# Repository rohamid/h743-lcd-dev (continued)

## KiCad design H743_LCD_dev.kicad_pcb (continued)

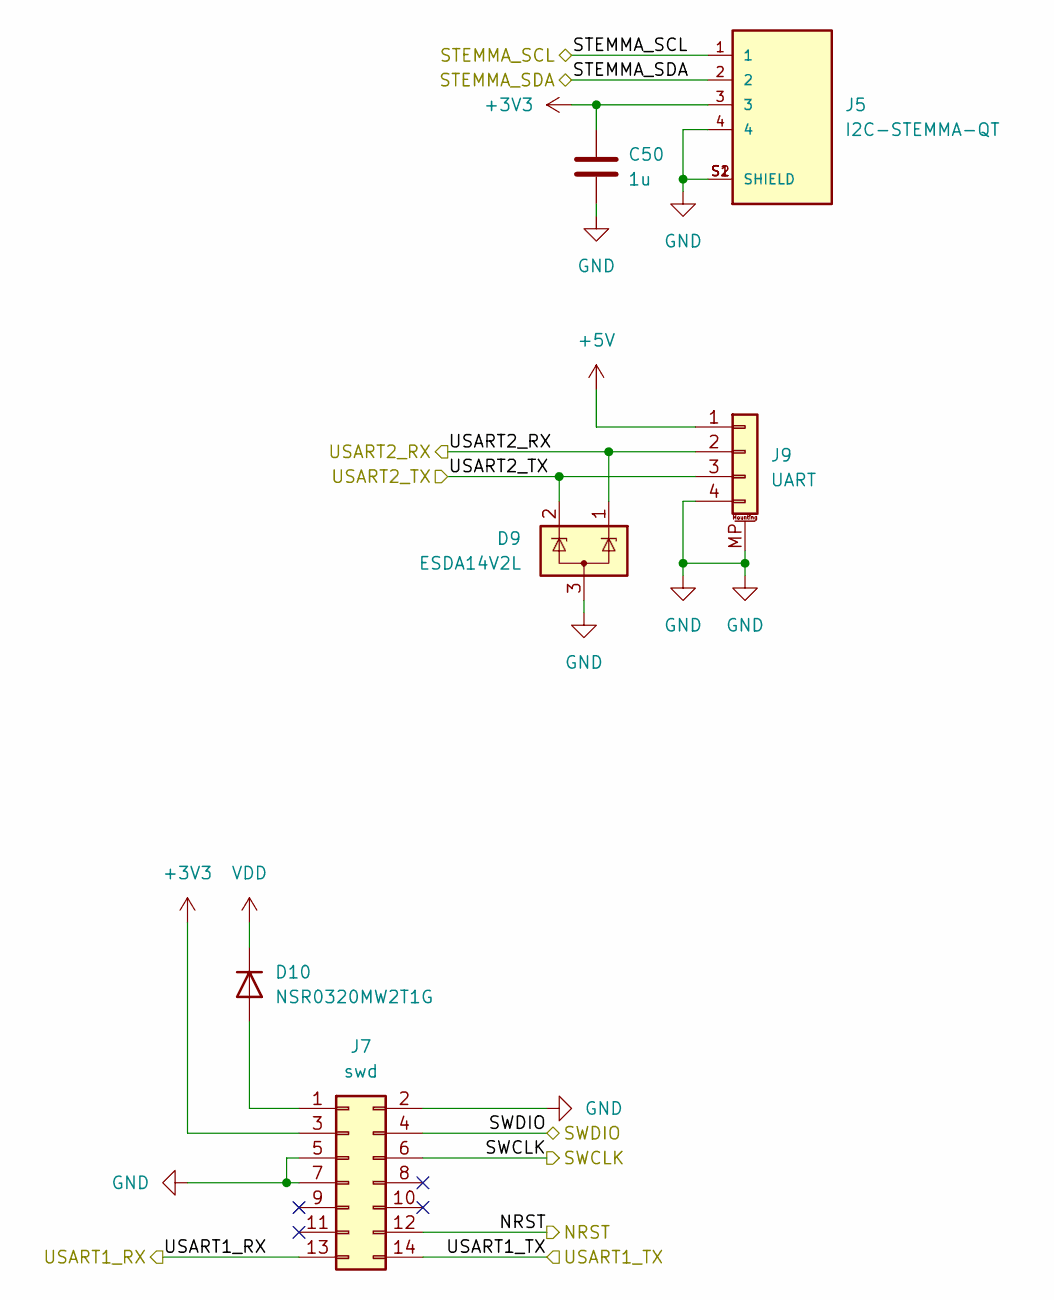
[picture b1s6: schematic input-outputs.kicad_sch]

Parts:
C50: 1u; C_0603_1608Metric; JLCPCB Part # C15849
D9: ESDA14V2L; SOT-23; JLCPCB Part # C2682282
D10: NSR0320MW2T1G; D_SOD-323; JLCPCB Part # C48192
J5: I2C-STEMMA-QT; JST_SM04B-SRSS-TB_LF__SN_; JLCPCB Part # C160404
J7: swd; PinHeader_2x07_P1.27mm_Vertical_SMD; JLCPCB Part # C2881912
J9: UART; S4BXHSM4TBLFSN; JLCPCB Part # C146120

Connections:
+3V3: C50.1, J5.3, J7.3; also elsewhere on the board
+5V: J9.1
/IO/NRST: J7.12; also elsewhere on the board
/IO/STEMMA_SCL: J5.1; also elsewhere on the board
/IO/STEMMA_SDA: J5.2; also elsewhere on the board
/IO/SWCLK: J7.6; also elsewhere on the board
/IO/SWDIO: J7.4; also elsewhere on the board
/IO/USART1_RX: J7.13; also elsewhere on the board
/IO/USART1_TX: J7.14; also elsewhere on the board
/IO/USART2_RX: D9.1 (K), J9.2; also elsewhere on the board
/IO/USART2_TX: D9.2 (K), J9.3; also elsewhere on the board
GND: C50.2, D9.3 (A), J5.4, J5.S1 (SHIELD), J5.S2 (SHIELD), J7.2, J7.5, J7.7, J9.4, J9.MP (MountPin); also elsewhere on the board
unnamed: D10.2 (A), J7.1
VDD: D10.1 (K); also elsewhere on the board

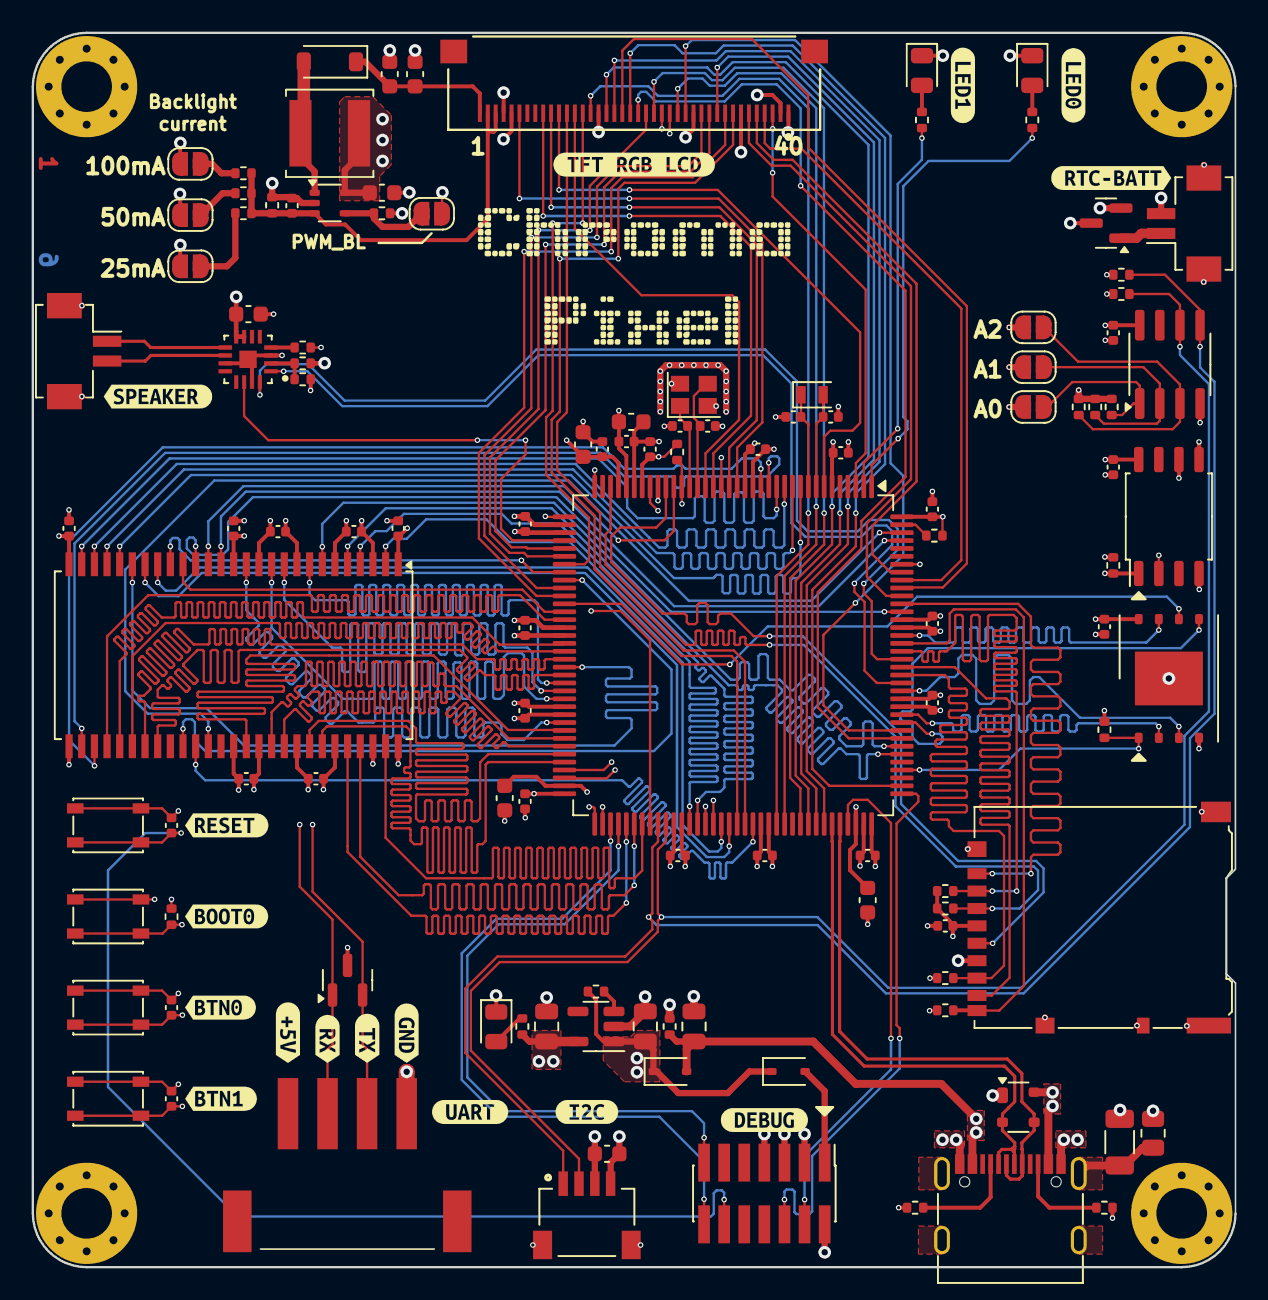
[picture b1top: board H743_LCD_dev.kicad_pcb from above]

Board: 6 copper layers, 76.0 x 78.0 mm, 136 parts (0 on the bottom side), 138 nets.

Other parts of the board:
kibuzzard-6641D1A5: G***; kibuzzard-6641D1A5
kibuzzard-6641D1AA: G***; kibuzzard-6641D1AA
kibuzzard-6641D1B0: G***; kibuzzard-6641D1B0
kibuzzard-6641D19D: G***; kibuzzard-6641D19D
kibuzzard-6642BE6C: G***; kibuzzard-6642BE6C
kibuzzard-6642BE54: G***; kibuzzard-6642BE54
kibuzzard-6642BE85: G***; kibuzzard-6642BE85
kibuzzard-6644A0DC: G***; kibuzzard-6644A0DC
kibuzzard-6644A120: G***; kibuzzard-6644A120
kibuzzard-6644A126: G***; kibuzzard-6644A126
kibuzzard-66458F9C: G***; kibuzzard-66458F9C
kibuzzard-66458F69: G***; kibuzzard-66458F69
kibuzzard-664329E8: G***; kibuzzard-664329E8
kibuzzard-664329F6: G***; kibuzzard-664329F6
kibuzzard-66417165: G***; kibuzzard-66417165
kibuzzard-66417197: G***; kibuzzard-66417197

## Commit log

2024-05-02 Added UART, i2c, debug, NAND Flash, NOR Flash, EEPROM, SD-Card
2024-05-02 Added I2S Audio amplifier
2024-05-03 Add net class, not clear yet
2024-05-05 Edited PCB
2024-05-10 Finish high speed sdram tracks
2024-05-12 Finish sdram, LCD, SD-card, QSPI, I2S tracks
2024-05-13 Looks like FPC should be changed to XF2M-4015-1A
2024-05-13 Changed the FPC footprint and uart, added RTC battery connector
2024-05-14 Added UART esd
2024-05-15 All clear (need to verify). LCD backlight driver left untracked
2024-05-15 All clear (need verification), need add capacitor next to I2C conn, verify I2S gain
2024-05-16 Finished. 1st version, ordered 1st batch
2024-07-26 Added docs
2024-07-26 Add schematic as pdf
